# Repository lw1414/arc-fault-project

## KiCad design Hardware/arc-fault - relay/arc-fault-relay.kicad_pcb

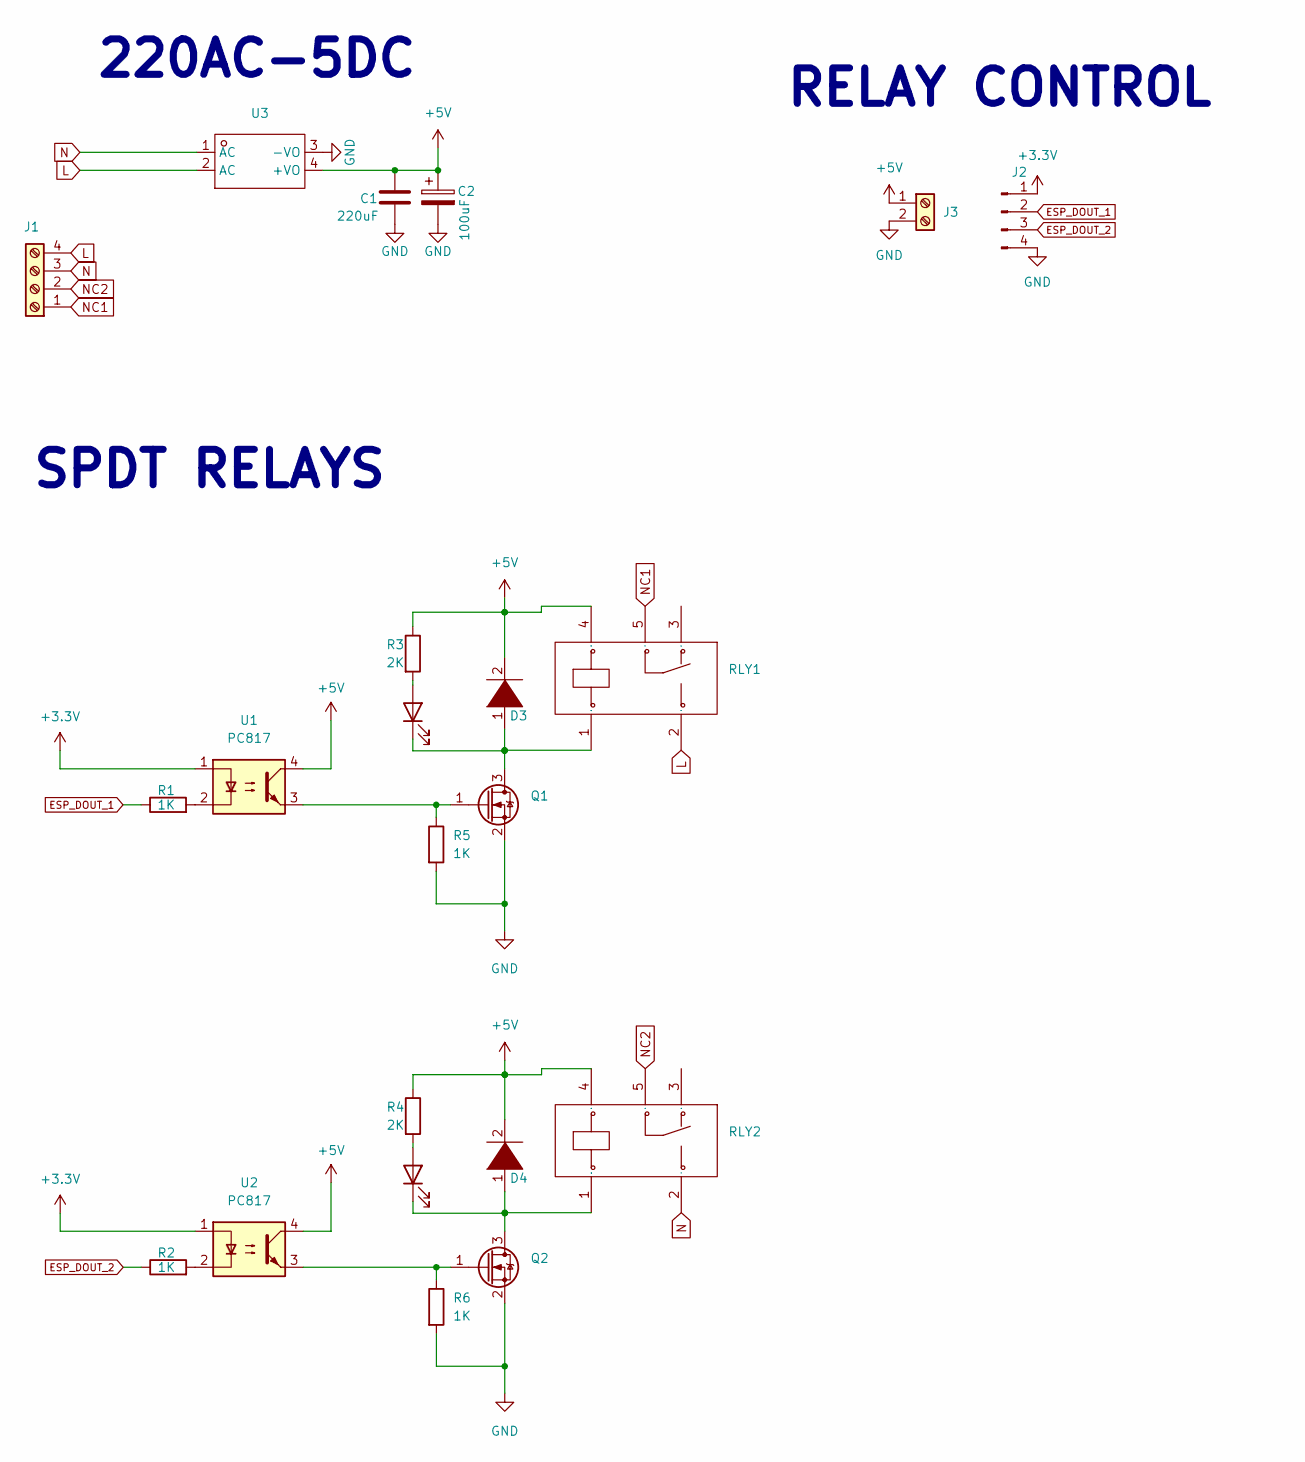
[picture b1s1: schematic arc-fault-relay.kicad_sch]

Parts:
C1: 220uF; C_1210_3225Metric_Pad1.33x2.70mm_HandSolder; LCSC C469553
C2: 100uF; C_0805_2012Metric_Pad1.18x1.45mm_HandSolder; LCSC C141660
D1, D2: LED; LED_0805_2012Metric_Pad1.15x1.40mm_HandSolder; LCSC C2297
D3, D4: 1N4001; D_SOD-123F; LCSC C2892326
J1: Screw_Terminal_01x04; Samtec_HPM-04-01-x-S_Straight_1x04_Pitch5.08mm
J2: Conn_01x04_Pin; PinHeader_1x02_P2.54mm_Vertical
J3: PinHeader_1x02_P2.54mm_Vertical
Q1, Q2: Q_NMOS_Depletion_GSD; SOT-23-3; LCSC C75882
R1, R2, R5, R6: 1K; R_0603_1608Metric_Pad0.98x0.95mm_HandSolder; LCSC C21190
R3, R4: 2K; R_0603_1608Metric_Pad0.98x0.95mm_HandSolder; LCSC C22975
RLY1, RLY2: RELAY-TH_SRD-XXVDC-XL-C; Manufacturer Part SRD-05VDC-SL-C; LCSC Part Name 蓝色 单组转换型继电器
U1, U2: PC817; APC-817xx-SL_AMB; LCSC C66405
U3: PWRM-TH_HLK-5M05; Manufacturer Part HLK-5M05; LCSC Part Name 5W超小型系列模块电源

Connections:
+3.3V: J2.1, U1.1, U2.1
+5V: C1.1, C2.1, D3.2 (A), D4.2 (A), J3.1, R3.1, R4.1, RLY1.4, RLY2.4, U1.4, U2.4, U3.4 (+VO)
ESP_DOUT_1: J2.2, R1.1
ESP_DOUT_2: J2.3, R2.1
GND: C1.2, C2.2, J2.4, J3.2, Q1.2 (S), Q2.2 (S), R5.2, R6.2, U3.3 (-VO)
L: J1.4, RLY1.2, U3.2 (AC)
N: J1.3, RLY2.2, U3.1 (AC)
NC1: J1.1, RLY1.5
NC2: J1.2, RLY2.5
unnamed: D1.2 (A), R3.2
unnamed: D1.1 (K), D3.1 (K), Q1.3 (D), RLY1.1
unnamed: D2.2 (A), R4.2
unnamed: D2.1 (K), D4.1 (K), Q2.3 (D), RLY2.1
unnamed: Q1.1 (G), R5.1, U1.3
unnamed: Q2.1 (G), R6.1, U2.3
unnamed: R1.2, U1.2
unnamed: R2.2, U2.2

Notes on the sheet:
220AC-5DC
RELAY CONTROL
SPDT RELAYS

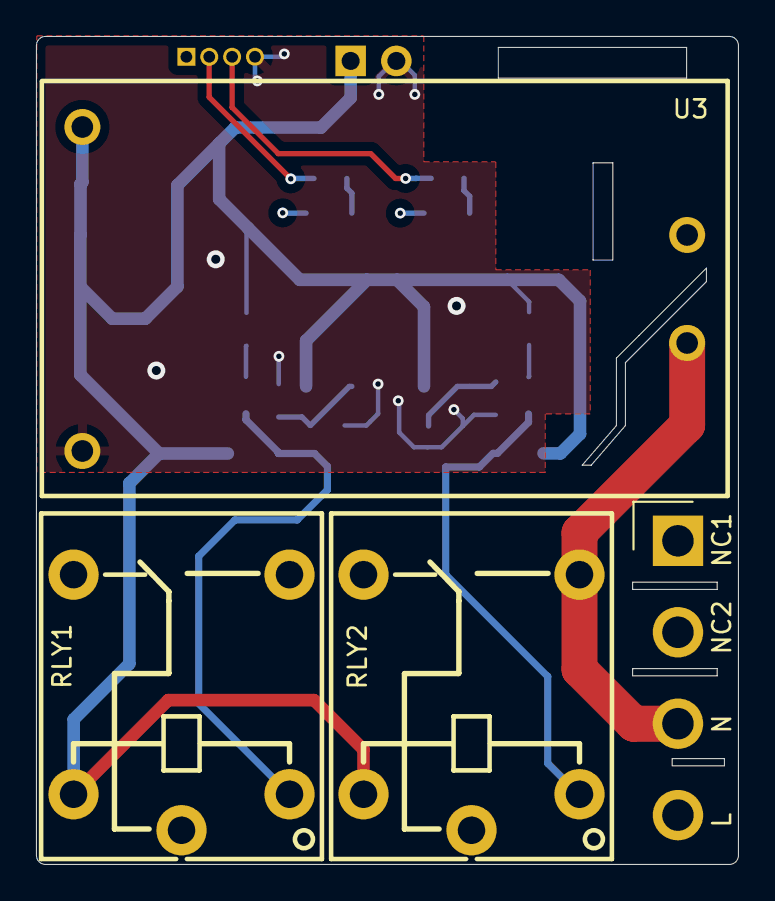
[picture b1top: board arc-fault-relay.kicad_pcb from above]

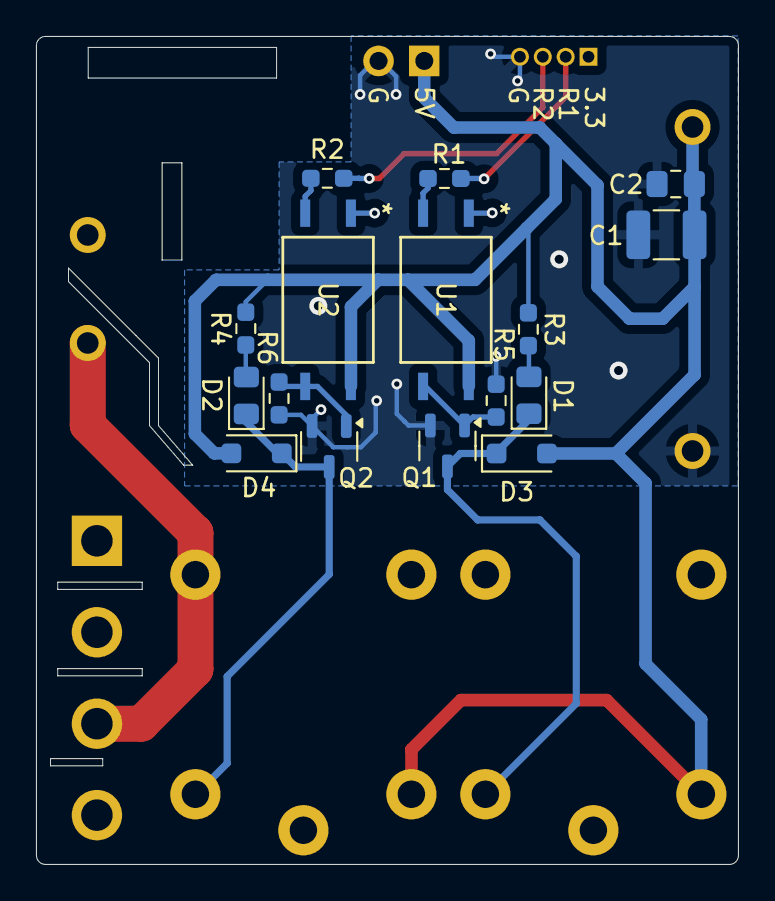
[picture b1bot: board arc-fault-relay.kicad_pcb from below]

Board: 4 copper layers, 39.0 x 46.0 mm, 22 parts (16 on the bottom side), 17 nets.

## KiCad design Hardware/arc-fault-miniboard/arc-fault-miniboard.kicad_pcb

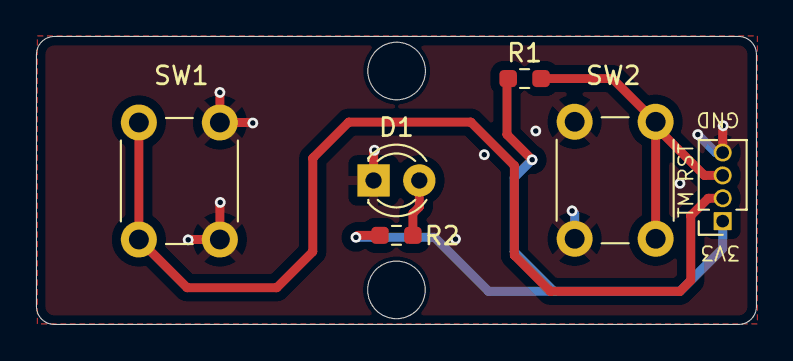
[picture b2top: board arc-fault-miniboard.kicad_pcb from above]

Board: 2 copper layers, 40.0 x 16.0 mm, 6 parts (0 on the bottom side), 5 nets.

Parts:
D1: LED; LED_D3.0mm
J5: Conn_01x04_Pin; PinSocket_1x04_P1.27mm_Vertical
R1, R2: 1K; R_0603_1608Metric_Pad0.98x0.95mm_HandSolder
SW1, SW2: SW_Push; SW_PUSH_6mm_H9.5mm

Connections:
+3.3V: J5.1, R1.2, R2.1
ESP_EN: J5.2, SW1.1
ESP_RELAY_TRIG: J5.3, R1.1, SW2.1
GND: D1.1 (K), J5.4, SW1.2, SW2.2
unnamed: D1.2 (A), R2.2

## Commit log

2025-11-20 block diagram ,flowchart and physical connection
2025-11-21 - added schematic
